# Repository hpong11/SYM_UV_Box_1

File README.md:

# SYM_UV_Box_1
Using Seeed Grove - 4-Digit Display library
https://github.com/Seeed-Studio/Grove_4Digital_Display

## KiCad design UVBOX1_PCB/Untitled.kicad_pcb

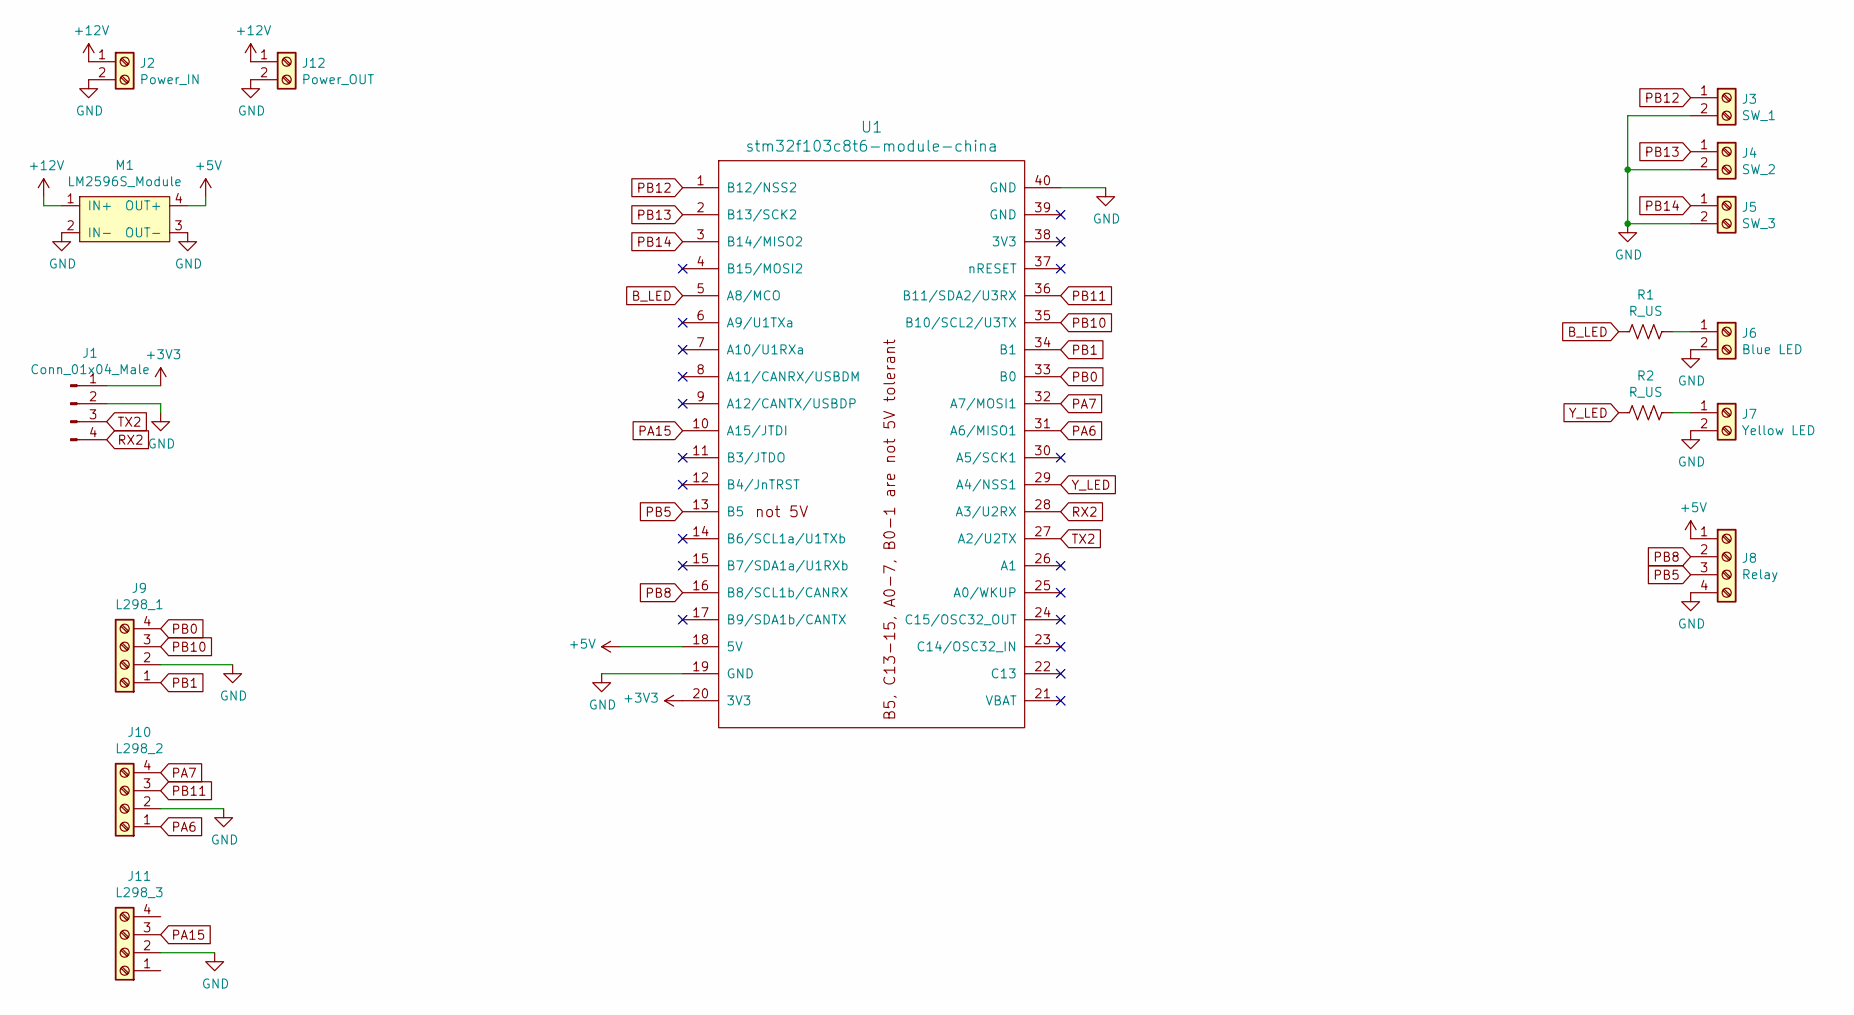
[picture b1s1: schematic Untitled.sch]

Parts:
J1: Conn_01x04_Male; PinHeader_1x04_P2.54mm_Vertical
J2: Power_IN; TerminalBlock_Phoenix_MKDS-1,5-2_1x02_P5.00mm_Horizontal
J3: SW_1; TerminalBlock_Phoenix_MKDS-1,5-2_1x02_P5.00mm_Horizontal
J4: SW_2; TerminalBlock_Phoenix_MKDS-1,5-2_1x02_P5.00mm_Horizontal
J5: SW_3; TerminalBlock_Phoenix_MKDS-1,5-2_1x02_P5.00mm_Horizontal
J6: Blue LED; TerminalBlock_Phoenix_MKDS-1,5-2_1x02_P5.00mm_Horizontal
J7: Yellow LED; TerminalBlock_Phoenix_MKDS-1,5-2_1x02_P5.00mm_Horizontal
J8: Relay; TerminalBlock_Phoenix_MKDS-1,5-4_1x04_P5.00mm_Horizontal
J9: L298_1; TerminalBlock_Phoenix_MKDS-1,5-4_1x04_P5.00mm_Horizontal
J10: L298_2; TerminalBlock_Phoenix_MKDS-1,5-4_1x04_P5.00mm_Horizontal
J11: L298_3; TerminalBlock_Phoenix_MKDS-1,5-4_1x04_P5.00mm_Horizontal
J12: Power_OUT; TerminalBlock_Phoenix_MKDS-1,5-2_1x02_P5.00mm_Horizontal
M1: LM2596S_Module; HW-411
R1, R2: R_US; R_Axial_DIN0207_L6.3mm_D2.5mm_P10.16mm_Horizontal
U1: stm32f103c8t6-module-china; Stm32f103_module

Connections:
+3V3: J1.1, U1.20 (3V3)
+5V: J8.1, M1.4 (OUT+), U1.18 (5V)
+12V: J2.1, J12.1, M1.1 (IN+)
B_LED: R1.2, U1.5 (A8/MCO)
GND: J1.2, J2.2, J3.2, J4.2, J5.2, J6.2, J7.2, J8.4, J9.2, J10.2, J11.2, J12.2, M1.2 (IN-), M1.3 (OUT-), U1.19 (GND), U1.40 (GND)
unnamed: J6.1, R1.1
unnamed: J7.1, R2.1
PA6: J10.1, U1.31 (A6/MISO1)
PA7: J10.4, U1.32 (A7/MOSI1)
PA15: J11.3, U1.10 (A15/JTDI)
PB0: J9.4, U1.33 (B0)
PB1: J9.1, U1.34 (B1)
PB5: J8.3, U1.13 (B5)
PB8: J8.2, U1.16 (B8/SCL1b/CANRX)
PB10: J9.3, U1.35 (B10/SCL2/U3TX)
PB11: J10.3, U1.36 (B11/SDA2/U3RX)
PB12: J3.1, U1.1 (B12/NSS2)
PB13: J4.1, U1.2 (B13/SCK2)
PB14: J5.1, U1.3 (B14/MISO2)
RX2: J1.4, U1.28 (A3/U2RX)
TX2: J1.3, U1.27 (A2/U2TX)
Y_LED: R2.2, U1.29 (A4/NSS1)

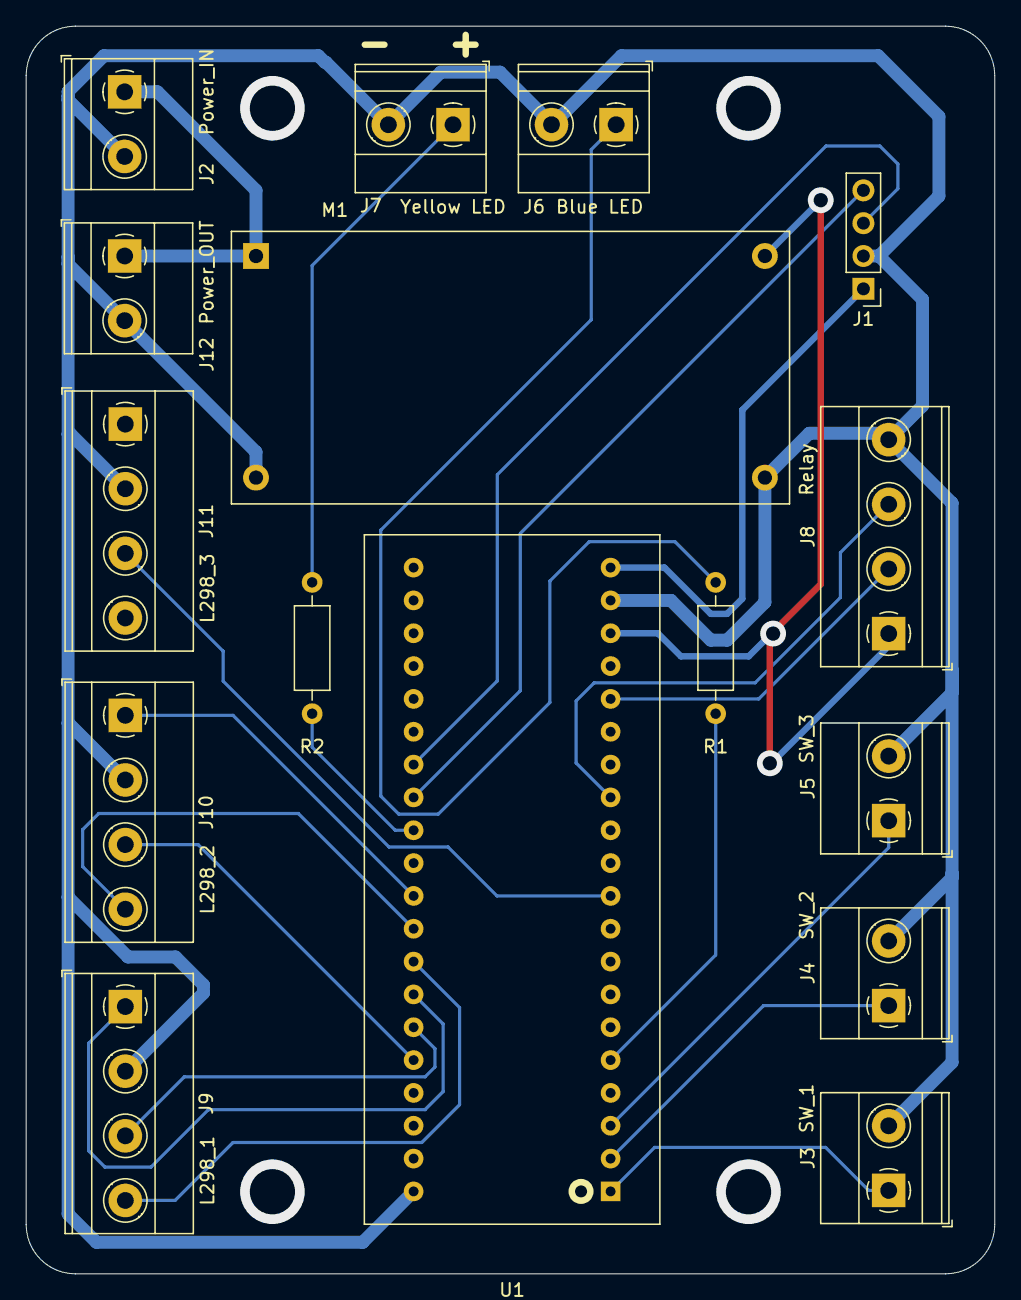
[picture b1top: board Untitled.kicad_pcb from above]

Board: 2 copper layers, 74.9 x 96.5 mm, 16 parts (0 on the bottom side), 22 nets.

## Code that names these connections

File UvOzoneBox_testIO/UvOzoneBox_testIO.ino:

#define R_LED PA8
#define G_LED PA4
#define SW_U PB12
#define SW_D PB13
#define SW_E PB14
#define F_FAN PA15
#define UV_FAN1 PA7
#define UV_FAN2 PA6
#define OZ_FAN1 PB0
#define OZ_FAN2 PB1
#define UV_LAMP PB8
#define OZ_LAMP PB5
#include "TM1637.h"
#define CLK PA0//pins definitions for TM1637 and can be changed to other ports
#define DIO PA1
TM1637 Disp7(CLK,DIO);

int8_t NumTab[] = {0,1,2,3,4,5,6,7,8,9,10,11,12,13,14,15};//0~9,A,b,C,d,E,F
int8_t ListDisp[4];

void Seven_Segment_Display(void);

void setup() {
  Disp7.init();
  Disp7.set(BRIGHT_TYPICAL);//BRIGHT_TYPICAL = 2,BRIGHT_DARKEST = 0,BRIGHTEST = 7;
  
  pinMode(F_FAN, OUTPUT);
  digitalWrite(F_FAN, 0);
  pinMode(R_LED, OUTPUT);
  pinMode(G_LED, OUTPUT);
  pinMode(SW_U, INPUT_PULLUP);
  pinMode(SW_D, INPUT_PULLUP);
  pinMode(SW_E, INPUT_PULLUP);
  pinMode(PB11, OUTPUT);
  pinMode(PB10, OUTPUT);
  digitalWrite(PB11, HIGH);
  digitalWrite(PB10, HIGH);
  pinMode(UV_FAN1, PWM);
  pinMode(UV_FAN2, PWM);
  pinMode(OZ_FAN1, PWM);
  pinMode(OZ_FAN2, PWM);
  pinMode(UV_LAMP, OUTPUT);
  pinMode(OZ_LAMP, OUTPUT);
  Timer1.setPrescaleFactor(40);
  Timer1.setOverflow(65454);
  
  
  Serial.begin(115200);

}

void loop() {
  digitalWrite(R_LED, 1);
  digitalWrite(G_LED, 1);
  
  digitalWrite(UV_LAMP, HIGH);
  digitalWrite(OZ_LAMP, LOW);
  digitalWrite(F_FAN, 1);
  pwmWrite(UV_FAN1, 25000);
  pwmWrite(UV_FAN2, 25000);
  pwmWrite(OZ_FAN1, 0);
  pwmWrite(OZ_FAN2, 0);
  delay(10000);

  digitalWrite(UV_LAMP, LOW);
  digitalWrite(OZ_LAMP, HIGH);
  digitalWrite(F_FAN, 1);
  pwmWrite(UV_FAN1, 0);
  pwmWrite(UV_FAN2, 0);
  pwmWrite(OZ_FAN1, 50000);
  pwmWrite(OZ_FAN2, 50000);
  delay(10000);
}

void Seven_Segment_Display(void){
  tm1637.display(0,ListDisp[0]);
  tm1637.display(1,ListDisp[1]);
  tm1637.display(2,ListDisp[2]);
  tm1637.display(3,ListDisp[3]);
}

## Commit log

2021-10-22 First
2021-10-23 Complete1_NotTest
2021-10-25 Complete1 Tested
2021-11-04 Beep Tested
2021-11-04 Complete +PCB
